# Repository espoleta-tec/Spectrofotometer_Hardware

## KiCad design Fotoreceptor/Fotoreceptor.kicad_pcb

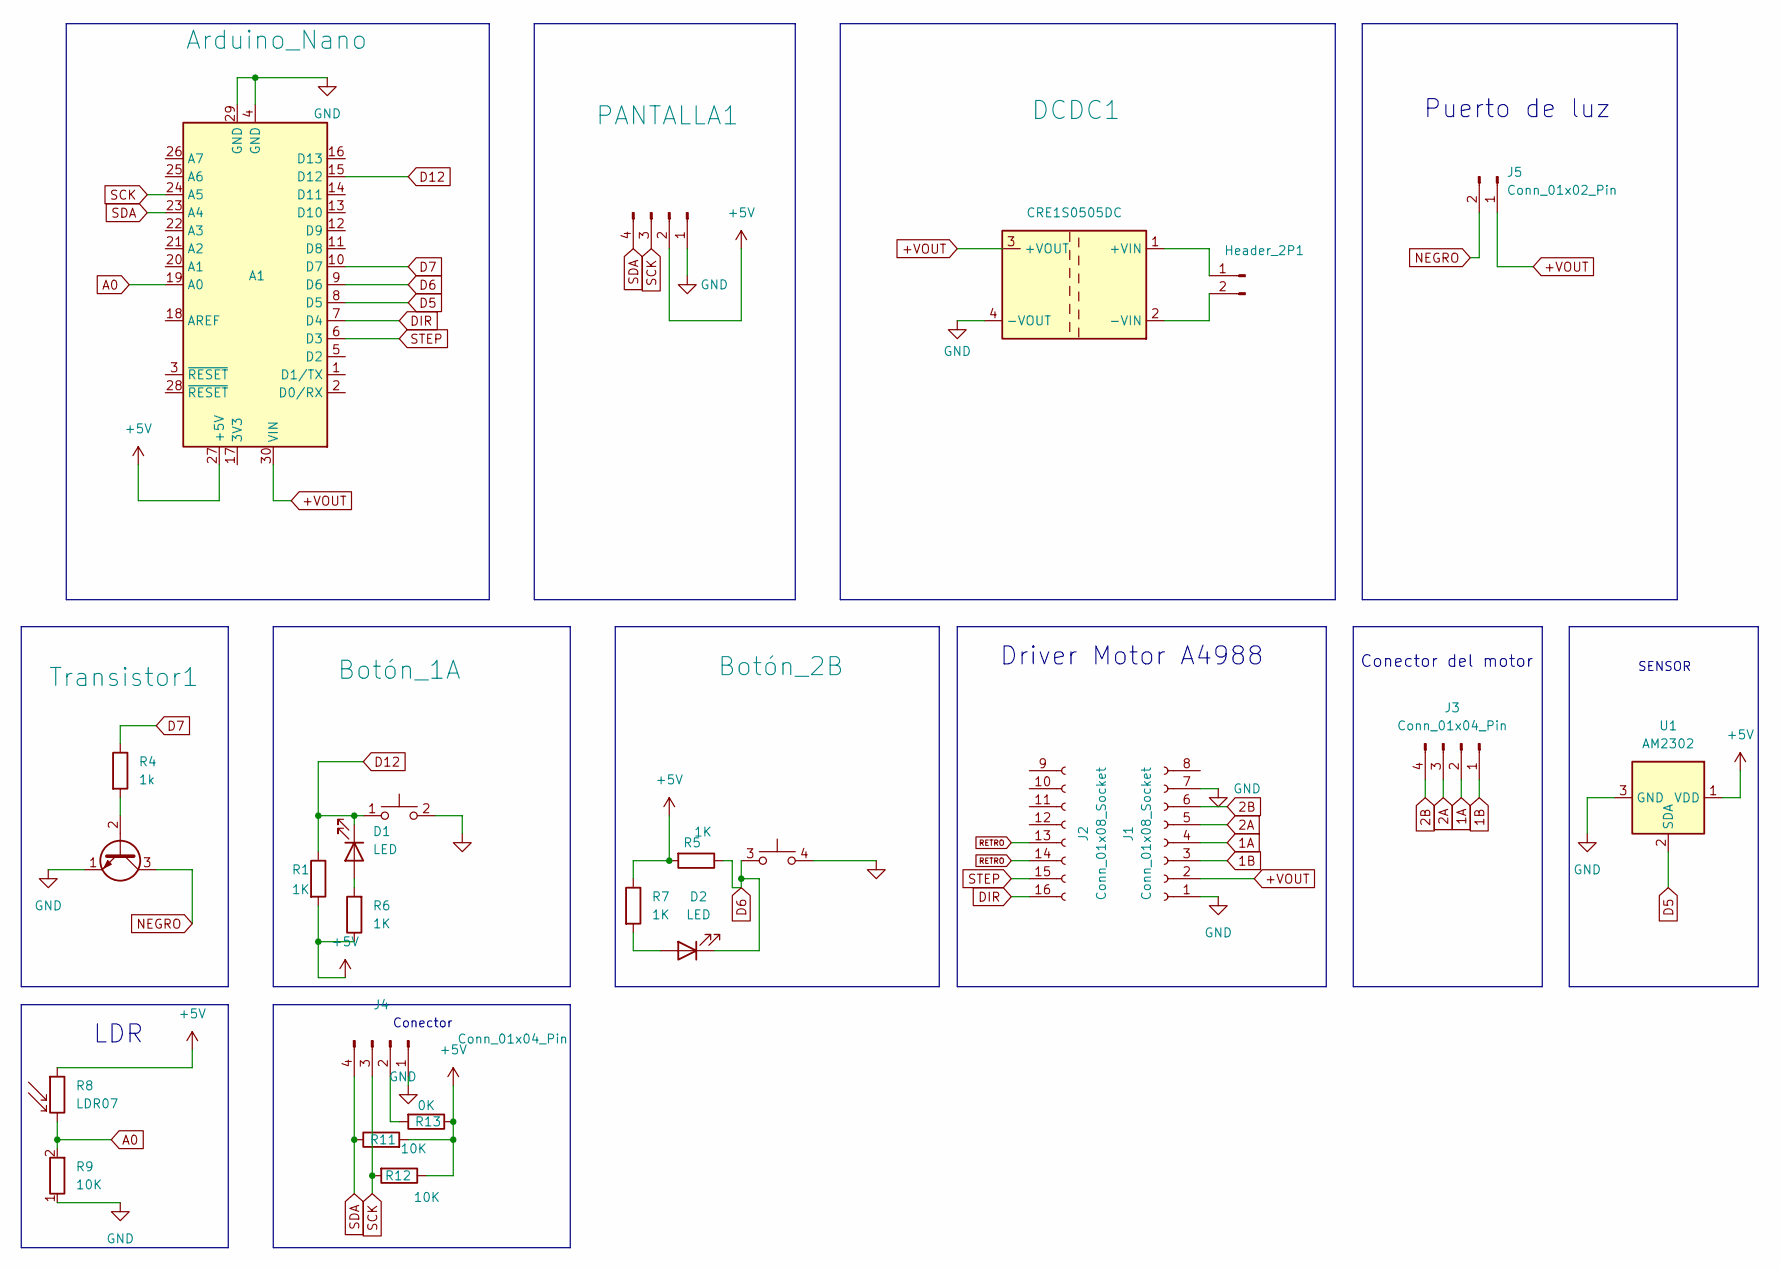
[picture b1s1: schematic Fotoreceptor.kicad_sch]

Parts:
A1: Arduino_Nano
Botón_1, Botón_2: SW_Push_Dual_x2; SW_Cherry_MX_1.25u_Plate
D1, D2: LED; LED_D1.8mm_W3.3mm_H2.4mm
DCDC1: CRE1S0505DC; Placa transformada
Header_2P1: Conn_01x02_Pin; PinHeader_1x02_P2.54mm_Horizontal
J1, J2: Conn_01x08_Socket; PinSocket_1x08_P2.54mm_Vertical
J3, J4: Conn_01x04_Pin; PinHeader_1x04_P2.54mm_Vertical
J5: Conn_01x02_Pin; PinHeader_1x02_P2.54mm_Vertical
PANTALLA1: Conn_01x04_Pin; PinSocket_1x04_P2.54mm_Vertical
R1, R5, R6, R7: 1K; R_1206_3216Metric
R4: 1k; R_1206_3216Metric
R8: LDR07; R_LDR_5.1x4.3mm_P3.4mm_Vertical
R9, R11, R12: 10K; R_1206_3216Metric
R13: 0K; R_1206_3216Metric
Transistor1: PN2222A; TO-92_Inline
U1: AM2302; ASAIR_AM2302_P2.54mm_Vertical

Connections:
1A: J1.4 (1A), J3.2
1B: J1.3 (1B), J3.1
2A: J1.5 (2A), J3.3
2B: J1.6 (2B), J3.4
+5V: A1.27 (+5V), PANTALLA1.2, R1.2, R5.2, R6.1, R7.1, R8.1, R11.2, R12.1, R13.1, U1.1 (VDD)
+VOUT: A1.30 (VIN), DCDC1.3 (+VOUT), J1.2 (VVD), J5.1
A0: A1.19 (A0), R8.2, R9.2
D5: A1.8 (D5), U1.2 (SDA)
D6: A1.9 (D6), Botón_2.3 (C), D2.1 (K), R5.1
D7: A1.10 (D7), R4.1
D12: A1.15 (D12), Botón_1.1 (C), D1.1 (K), R1.1
DIR: A1.7 (D4), J2.16 (DIR)
GND: A1.4 (GND), A1.29 (GND), Botón_1.2 (D), Botón_2.4 (D), DCDC1.4 (-VOUT), J1.1 (GND), J1.7 (GND), J4.1, PANTALLA1.1, R9.1, Transistor1.1 (E), U1.3 (GND), U1.4 (GND)
NEGRO: J5.2, Transistor1.3 (C)
unnamed: D1.2 (A), R6.2
unnamed: D2.2 (A), R7.2
unnamed: DCDC1.1 (+VIN), Header_2P1.1
unnamed: DCDC1.2 (-VIN), Header_2P1.2
unnamed: J4.2, R13.2
unnamed: R4.2, Transistor1.2 (B)
RETRO: J2.13 (RESET), J2.14 (SLEEP)
SCK: A1.24 (A5), J4.3, PANTALLA1.3, R12.2
SDA: A1.23 (A4), J4.4, PANTALLA1.4, R11.1
STEP: A1.6 (D3), J2.15 (STEP)

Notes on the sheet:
Conector
Driver Motor A4988
SENSOR
Conector del motor
Puerto de luz
LDR

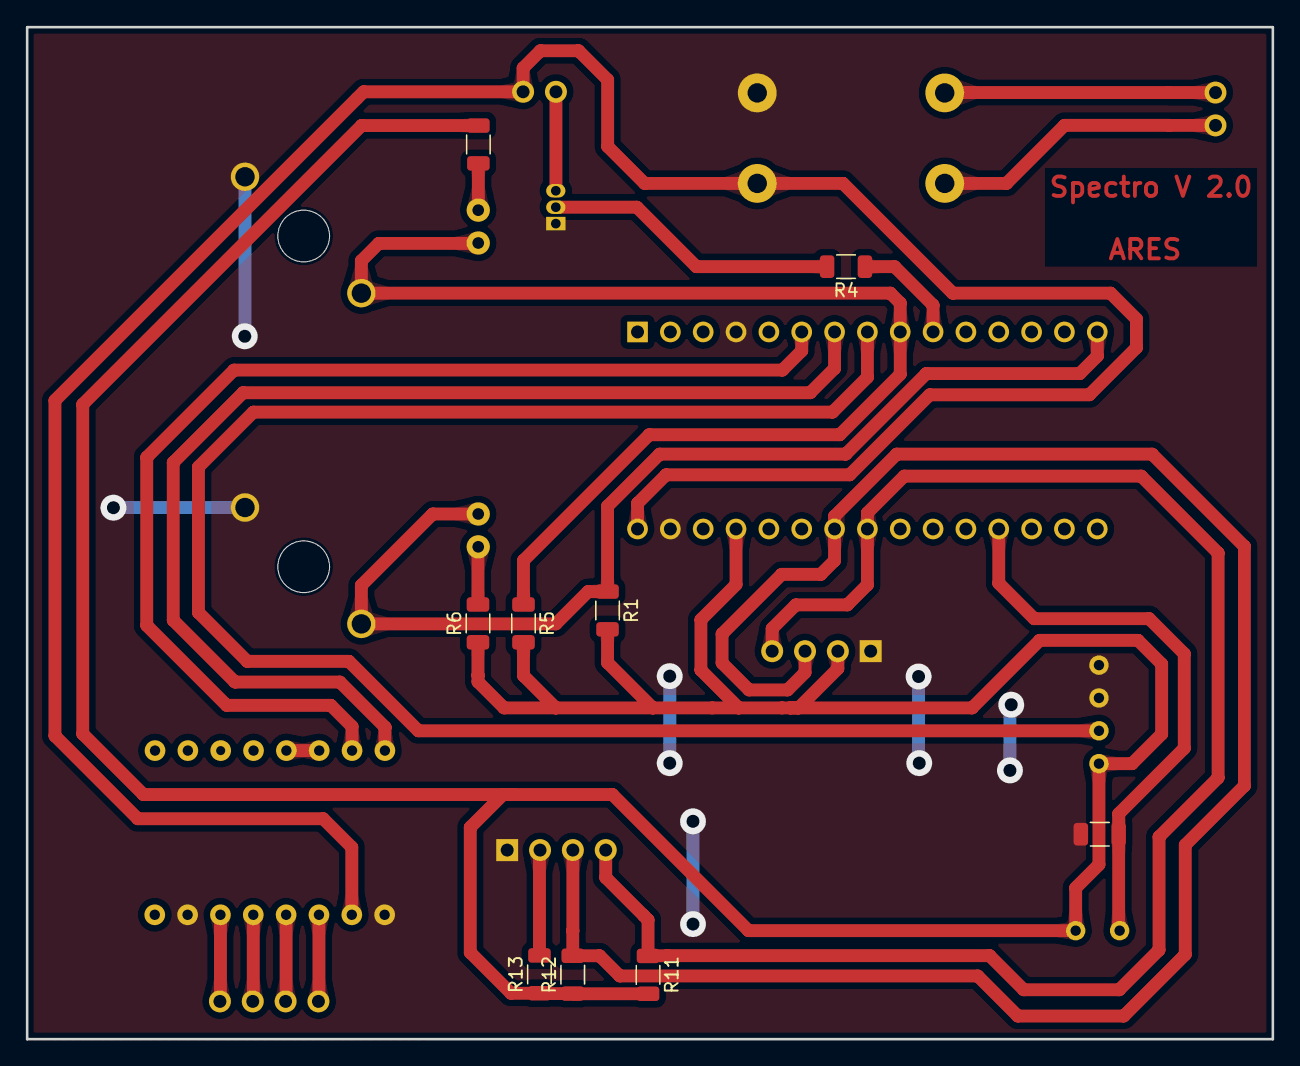
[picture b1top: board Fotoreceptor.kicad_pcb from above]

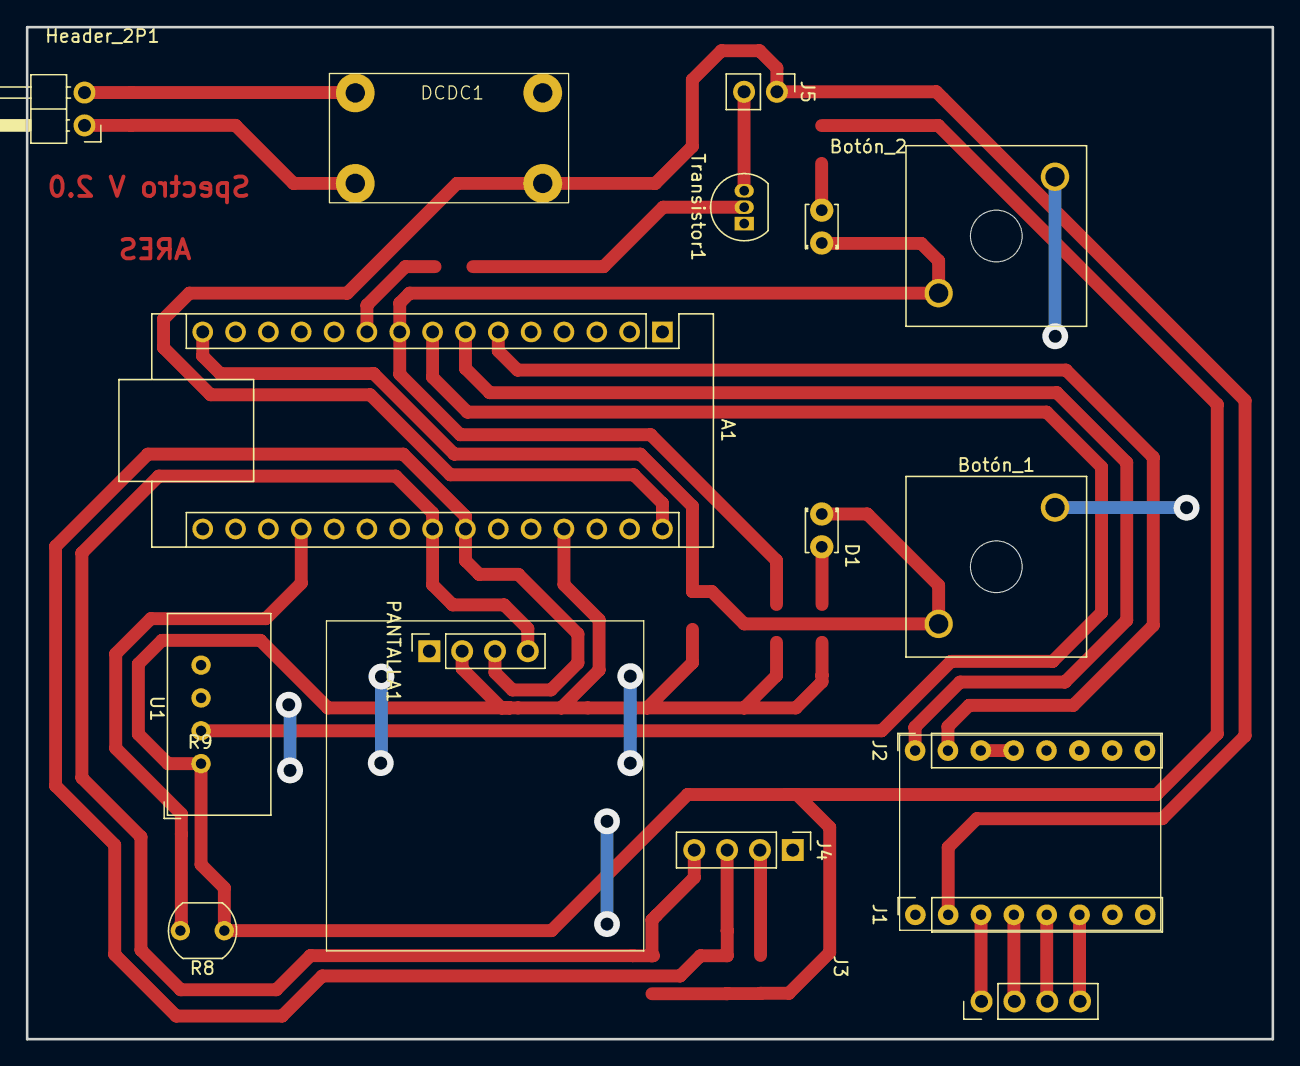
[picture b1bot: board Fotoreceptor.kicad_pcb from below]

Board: 2 copper layers, 96.3 x 78.3 mm, 25 parts (16 on the bottom side), 24 nets.

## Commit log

2025-08-23 primer co
2025-08-28 Hardware
